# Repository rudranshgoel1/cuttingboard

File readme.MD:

# RP2040 Devboard

### Why did I make it?
bcz i need more hardware projects in my portfolio and also because it seemed like a fun hardware project which was not at all beginner friendly but still pretty interesting.

### What was the hardest part about this ?
routing. routing was hell. nevertheless, we did it.

### assembly?
going to hand solder each thing, if you want to do pcba (i can't due to budget reasons), go to the production folder and get the BOM and CPL for jlcpcb pcba service.

Features:

- rp2040 chip
- usb-c for power
- flash memory/storage
- crystal occilator
- built in accelerometer for cool shit
- Custom PCB Art (really cool)
- led

### Schematic

### PCB 

### 3D view of all parts 

## BOM

[BOM](BOM.csv)

|Comment                    |Designator                         |Footprint                                  |JLCPCB Part #|Price  |Source     |
|---------------------------|-----------------------------------|-------------------------------------------|-------------|-------|-----------|
|1uF                        |C10,C1                             |C_0402_1005Metric                          |C52923       |$0.2420|JLCPCB PCBA|
|MCP1700x-330xxTT           |U4                                 |SOT-23                                     |C39051       |$2.0390|JLCPCB PCBA|
|33pF                       |C15,C16                            |C_0402_1005Metric                          |C1562        |$0.1140|JLCPCB PCBA|
|1K                         |R7,R5                              |R_0402_1005Metric                          |C11702       |$0.0780|JLCPCB PCBA|
|5.1K                       |R2,R1                              |R_0402_1005Metric                          |C25905       |$0.0860|JLCPCB PCBA|
|12MHz                      |Y1                                 |Crystal_SMD_3225-4Pin_3.2x2.5mm            |C9002        |$0.6629|JLCPCB PCBA|
|10uF                       |C13,C14                            |C_0402_1005Metric                          |C19702       |$0.7000|JLCPCB PCBA|
|RP2040                     |U1                                 |QFN-56-1EP_7x7mm_P0.4mm_EP3.2x3.2mm        |C2040        |$4.9625|JLCPCB PCBA|
|0.1uF                      |C8,C17,C12,C4,C3,C5,C6,C2,C11,C7,C9|C_0402_1005Metric                          |C1525        |$0.3575|JLCPCB PCBA|
|W25Q128JVS                 |U3                                 |Winbond_USON-8-1EP_3x2mm_P0.5mm_EP0.2x1.6mm|C2843335     |$7.8700|JLCPCB PCBA|
|10K                        |R6                                 |R_0402_1005Metric                          |C25744       |$0.0380|JLCPCB PCBA|
|USB_C_Receptacle_USB2.0_14P|J1                                 |USB_C_Receptacle_HRO_TYPE-C-31-M-12        |C165948      |$0.9280|JLCPCB PCBA|
|27                         |R4,R3                              |R_0402_1005Metric                          |C25100       |$0.0704|JLCPCB PCBA|
|SW_Push                    |SW1                                |SW_Push_SPST_NO_Alps_SKRK                  |C720477      |$0.5004|JLCPCB PCBA|

PCB Cost - $11.76 [ shipping included ]
Components Cost - $18.65

Final Price comes out to be 2,915.48 INR ($30.41)

## Total Pricing
(reviewers, i have a jlcpcb coupon for $15, so the pcb cost get's nullified, so the total cost for me is $18.65, but for others it would be the price given below)
The total price comes out to be 2,915.48 INR ($30.41) [ SHIPPING INCLUDED ]

I am going to hand solder all the components.

The pricing might slightly vary due to flash sales, and dollar market trends.

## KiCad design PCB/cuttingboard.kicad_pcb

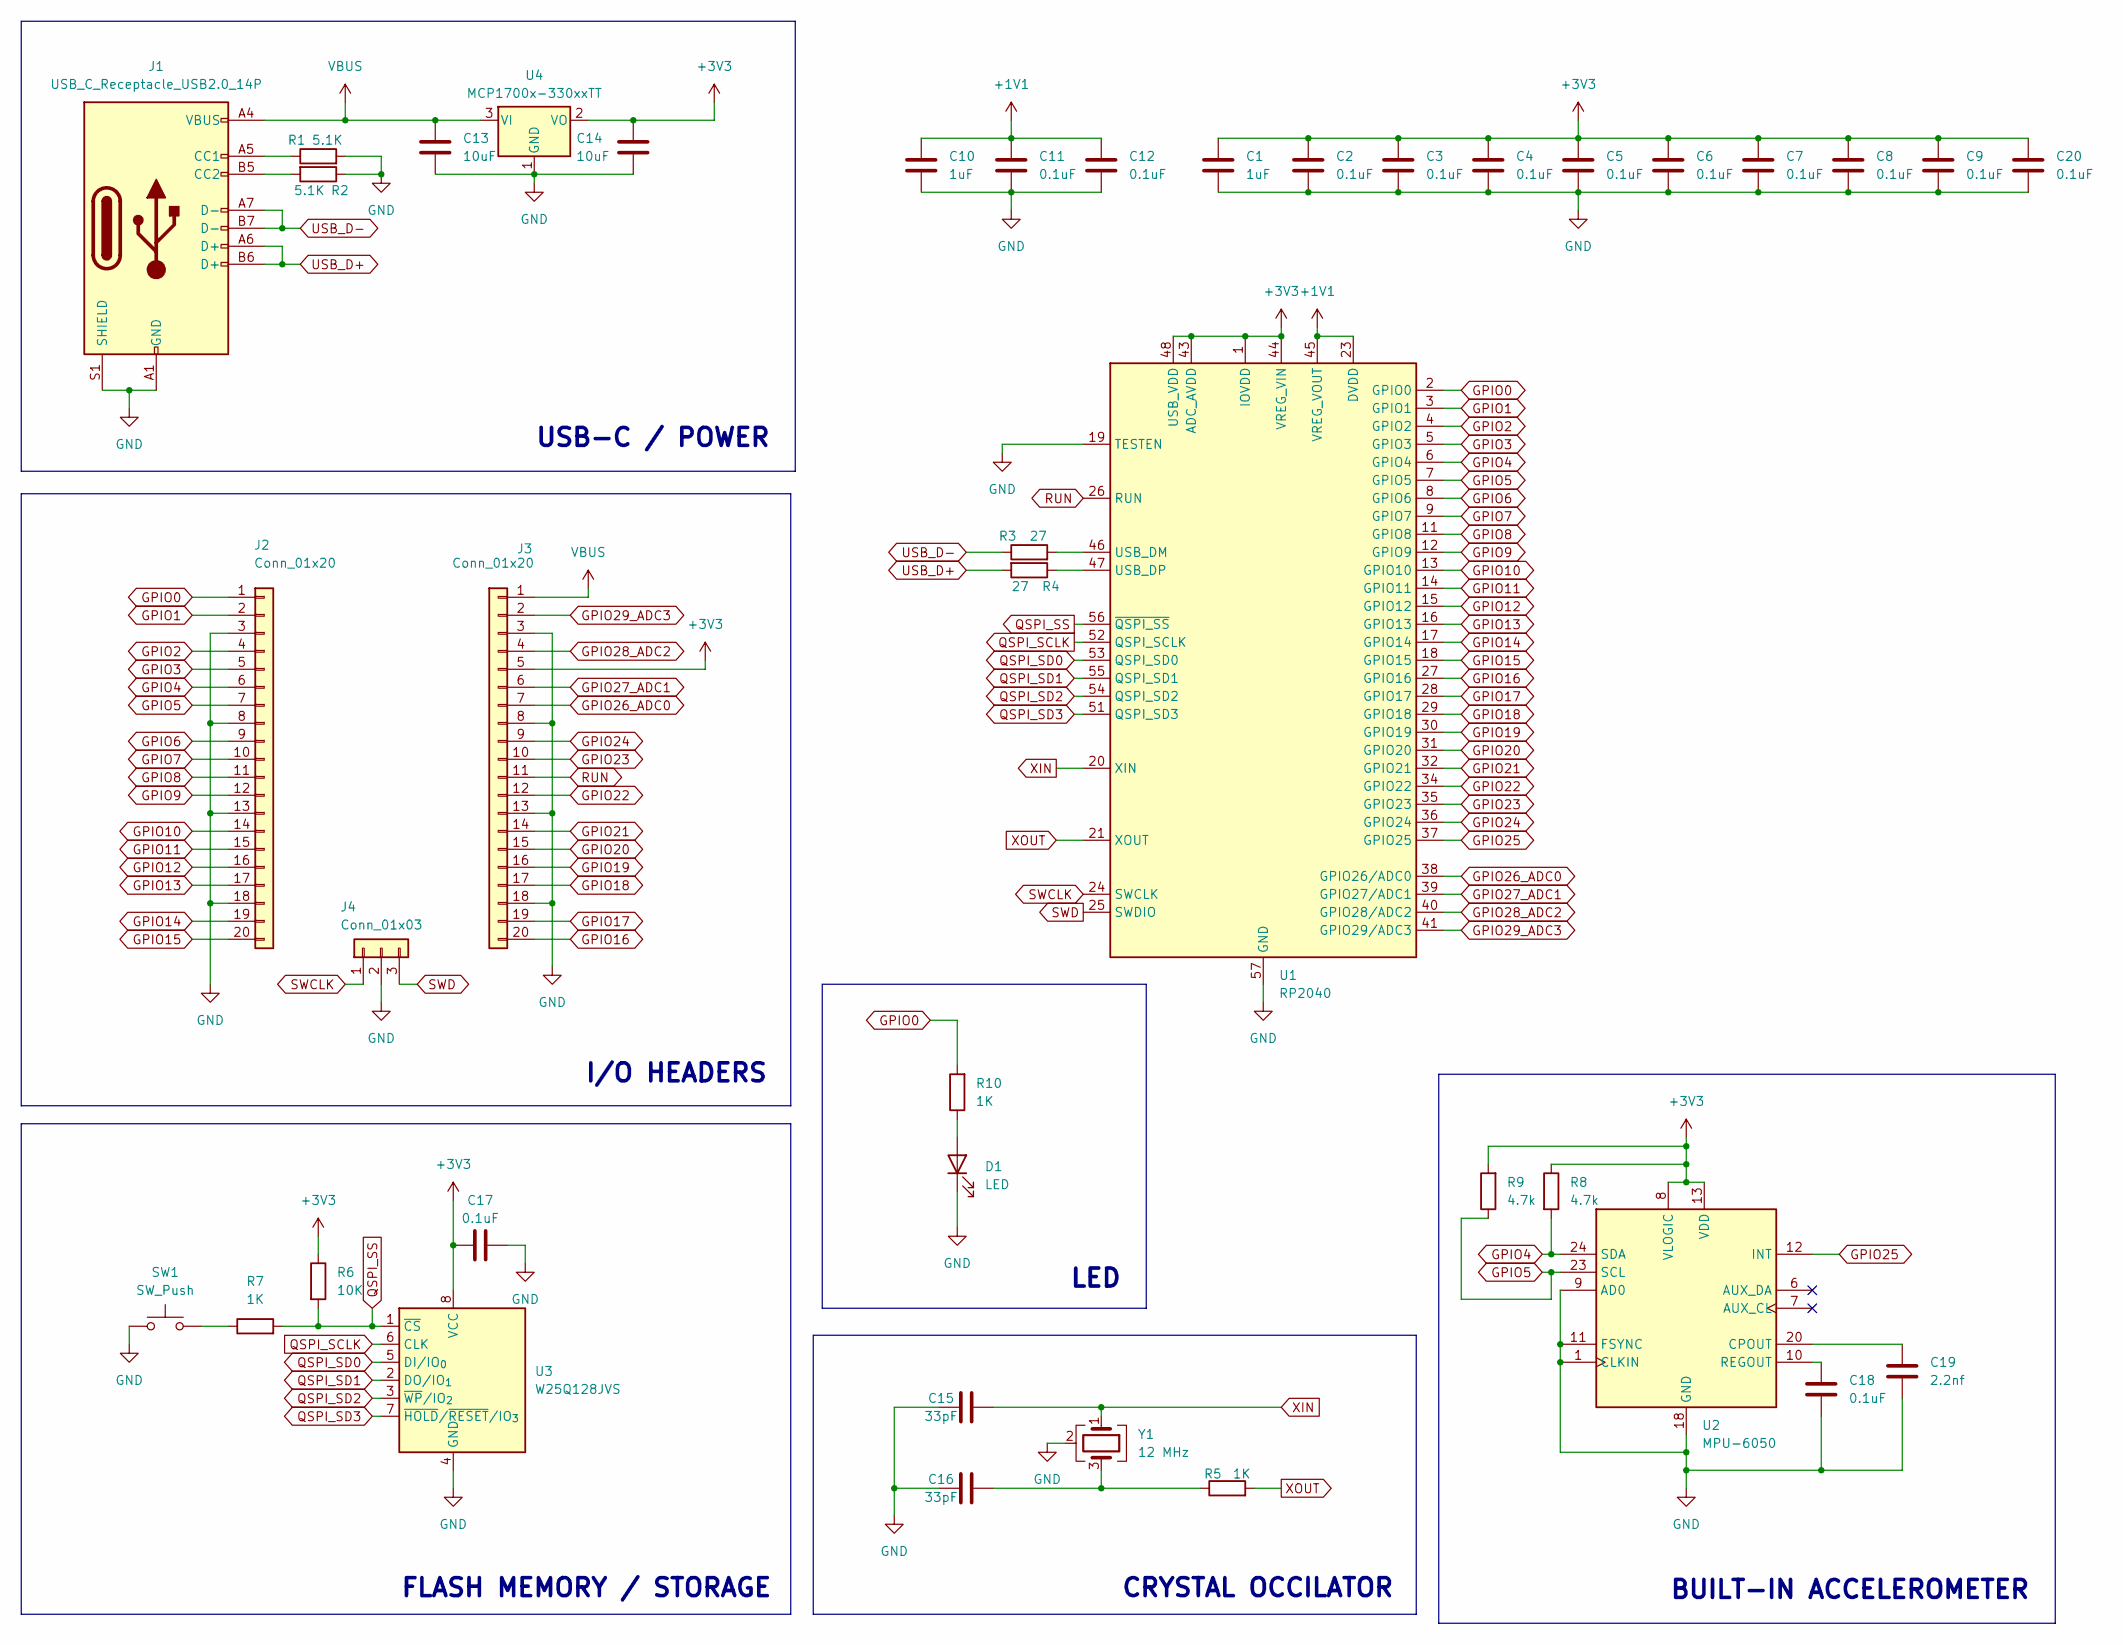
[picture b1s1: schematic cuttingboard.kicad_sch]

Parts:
C1, C10: 1uF; C_0402_1005Metric
C2, C3, C4, C5, C6, C7, C8, C9, C11, C12, C17, C18, C20: 0.1uF; C_0402_1005Metric
C13, C14: 10uF; C_0402_1005Metric
C15, C16: 33pF; C_0402_1005Metric
C19: 2.2nf; C_0402_1005Metric
D1: LED; LED_0805_2012Metric_Pad1.15x1.40mm_HandSolder
J1: USB_C_Receptacle_USB2.0_14P; USB_C_Receptacle_HRO_TYPE-C-31-M-12
J2, J3: Conn_01x20; PinHeader_1x20_P2.54mm_Vertical
J4: Conn_01x03; PinHeader_1x03_P2.54mm_Vertical
R1, R2: 5.1K; R_0402_1005Metric
R3, R4: 27; R_0402_1005Metric
R5, R7, R10: 1K; R_0402_1005Metric
R6: 10K; R_0402_1005Metric
R8, R9: 4.7k; R_0402_1005Metric
SW1: SW_Push; SW_Push_SPST_NO_Alps_SKRK
U1: RP2040; QFN-56-1EP_7x7mm_P0.4mm_EP3.2x3.2mm
U2: MPU-6050; InvenSense_QFN-24_4x4mm_P0.5mm
U3: W25Q128JVS; Winbond_USON-8-1EP_3x2mm_P0.5mm_EP0.2x1.6mm
U4: MCP1700x-330xxTT; SOT-23
Y1: 12 MHz; Crystal_SMD_3225-4Pin_3.2x2.5mm

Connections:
+1V1: C10.2, C11.2, C12.2, U1.23 (DVDD), U1.45 (VREG_VOUT), U1.50 (DVDD)
+3V3: C1.2, C2.2, C3.2, C4.2, C5.2, C6.2, C7.2, C8.2, C9.2, C14.1, C17.1, C20.2, J3.5, R6.1, R8.1, R9.2, U1.1 (IOVDD), U1.10 (IOVDD), U1.22 (IOVDD), U1.33 (IOVDD), U1.42 (IOVDD), U1.43 (ADC_AVDD), U1.44 (VREG_VIN), U1.48 (USB_VDD), U1.49 (IOVDD), U2.8 (VLOGIC), U2.13 (VDD), U3.8 (VCC), U4.2 (VO)
GND: C1.1, C2.1, C3.1, C4.1, C5.1, C6.1, C7.1, C8.1, C9.1, C10.1, C11.1, C12.1, C13.2, C14.2, C15.1, C16.1, C17.2, C18.1, C19.1, C20.1, D1.1 (K), J1.A1 (GND), J1.A12 (GND), J1.B1 (GND), J1.B12 (GND), J1.S1 (SHIELD), J2.3, J2.8, J2.13, J2.18, J3.3, J3.8, J3.13, J3.18, J4.2, R1.2, R2.1, SW1.1, U1.19 (TESTEN), U1.57 (GND), U2.1 (CLKIN), U2.9 (AD0), U2.11 (FSYNC), U2.18 (GND), U3.4 (GND), U4.1 (GND), Y1.2 (G), Y1.4 (G)
GPIO0: J2.1, R10.2, U1.2 (GPIO0)
GPIO1: J2.2, U1.3 (GPIO1)
GPIO2: J2.4, U1.4 (GPIO2)
GPIO3: J2.5, U1.5 (GPIO3)
GPIO4: J2.6, R8.2, U1.6 (GPIO4), U2.24 (SDA)
GPIO5: J2.7, R9.1, U1.7 (GPIO5), U2.23 (SCL)
GPIO6: J2.9, U1.8 (GPIO6)
GPIO7: J2.10, U1.9 (GPIO7)
GPIO8: J2.11, U1.11 (GPIO8)
GPIO9: J2.12, U1.12 (GPIO9)
GPIO10: J2.14, U1.13 (GPIO10)
GPIO11: J2.15, U1.14 (GPIO11)
GPIO12: J2.16, U1.15 (GPIO12)
GPIO13: J2.17, U1.16 (GPIO13)
GPIO14: J2.19, U1.17 (GPIO14)
GPIO15: J2.20, U1.18 (GPIO15)
GPIO16: J3.20, U1.27 (GPIO16)
GPIO17: J3.19, U1.28 (GPIO17)
GPIO18: J3.17, U1.29 (GPIO18)
GPIO19: J3.16, U1.30 (GPIO19)
GPIO20: J3.15, U1.31 (GPIO20)
GPIO21: J3.14, U1.32 (GPIO21)
GPIO22: J3.12, U1.34 (GPIO22)
GPIO23: J3.10, U1.35 (GPIO23)
GPIO24: J3.9, U1.36 (GPIO24)
GPIO25: U1.37 (GPIO25), U2.12 (INT)
GPIO26_ADC0: J3.7, U1.38 (GPIO26/ADC0)
GPIO27_ADC1: J3.6, U1.39 (GPIO27/ADC1)
GPIO28_ADC2: J3.4, U1.40 (GPIO28/ADC2)
GPIO29_ADC3: J3.2, U1.41 (GPIO29/ADC3)
unnamed: C16.2, R5.1, Y1.3
unnamed: D1.2 (A), R10.1
unnamed: J1.A5 (CC1), R1.1
unnamed: J1.B5 (CC2), R2.2
unnamed: R7.1, SW1.2
unnamed: R3.2, U1.46 (USB_DM)
unnamed: R4.1, U1.47 (USB_DP)
unnamed: C19.2, U2.20 (CPOUT)
unnamed: C18.2, U2.10 (REGOUT)
QSPI_SCLK: U1.52 (QSPI_SCLK), U3.6 (CLK)
QSPI_SD0: U1.53 (QSPI_SD0), U3.5 (DI/IO_{0})
QSPI_SD1: U1.55 (QSPI_SD1), U3.2 (DO/IO_{1})
QSPI_SD2: U1.54 (QSPI_SD2), U3.3 (~WP/IO_{2})
QSPI_SD3: U1.51 (QSPI_SD3), U3.7 (~HOLD/~RESET/IO_{3})
QSPI_SS: R6.2, R7.2, U1.56 (~QSPI_SS), U3.1 (~CS)
RUN: J3.11, U1.26 (RUN)
SWCLK: J4.1, U1.24 (SWCLK)
SWD: J4.3, U1.25 (SWDIO)
USB_D+: J1.A6 (D+), J1.B6 (D+), R4.2
USB_D-: J1.A7 (D-), J1.B7 (D-), R3.1
VBUS: C13.1, J1.A4 (VBUS), J1.A9 (VBUS), J1.B4 (VBUS), J1.B9 (VBUS), J3.1, U4.3 (VI)
XIN: C15.2, U1.20 (XIN), Y1.1
XOUT: R5.2, U1.21 (XOUT)

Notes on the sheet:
FLASH MEMORY / STORAGE
CRYSTAL OCCILATOR
LED
USB-C / POWER
I/O HEADERS
BUILT-IN ACCELEROMETER

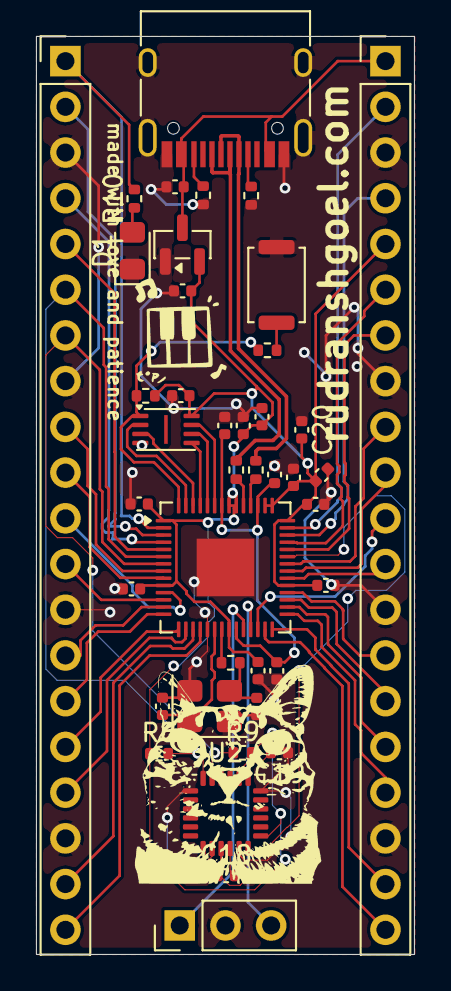
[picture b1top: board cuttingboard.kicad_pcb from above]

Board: 2 copper layers, 21.0 x 51.0 mm, 41 parts (0 on the bottom side), 56 nets.

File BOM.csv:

Comment,Designator,Footprint,JLCPCB Part #,Price,Source
1uF,"C10,C1",C_0402_1005Metric,C52923,$0.2420,JLCPCB PCBA
MCP1700x-330xxTT,U4,SOT-23,C39051,$2.0390,JLCPCB PCBA
33pF,"C15,C16",C_0402_1005Metric,C1562,$0.1140,JLCPCB PCBA
1K,"R7,R5",R_0402_1005Metric,C11702,$0.0780,JLCPCB PCBA
5.1K,"R2,R1",R_0402_1005Metric,C25905,$0.0860,JLCPCB PCBA
12MHz,Y1,Crystal_SMD_3225-4Pin_3.2x2.5mm,C9002,$0.6629,JLCPCB PCBA
10uF,"C13,C14",C_0402_1005Metric,C19702,$0.7000,JLCPCB PCBA
RP2040,U1,QFN-56-1EP_7x7mm_P0.4mm_EP3.2x3.2mm,C2040,$4.9625,JLCPCB PCBA
0.1uF,"C8,C17,C12,C4,C3,C5,C6,C2,C11,C7,C9",C_0402_1005Metric,C1525,$0.3575,JLCPCB PCBA
W25Q128JVS,U3,Winbond_USON-8-1EP_3x2mm_P0.5mm_EP0.2x1.6mm,C2843335,$7.8700,JLCPCB PCBA
10K,R6,R_0402_1005Metric,C25744,$0.0380,JLCPCB PCBA
USB_C_Receptacle_USB2.0_14P,J1,USB_C_Receptacle_HRO_TYPE-C-31-M-12,C165948,$0.9280,JLCPCB PCBA
27,"R4,R3",R_0402_1005Metric,C25100,$0.0704,JLCPCB PCBA
SW_Push,SW1,SW_Push_SPST_NO_Alps_SKRK,C720477,$0.5004,JLCPCB PCBA
